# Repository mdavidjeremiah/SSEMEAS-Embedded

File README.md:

# SSMEAS: Smart Sewage Level Monitoring

ESP32 + HC-SR04 reads the sewage level and alerts locally. A FastAPI backend stores the readings, applies the alert rules and sends WhatsApp messages. A plain HTML/CSS/JS dashboard shows it live.

```
ssmeas/
├── backend/                FastAPI + SQLite
│   ├── main.py             entry point (serves the API and the dashboard)
│   ├── app/
│   │   ├── config.py       settings from environment variables / .env
│   │   ├── db.py, repo.py  database and queries
│   │   ├── security.py     passwords, login tokens, rate limiting
│   │   ├── schemas.py      request validation
│   │   ├── routers/        auth, device (ESP32), dashboard, profile, admin, webhooks, live (WebSocket)
│   │   └── services/       status (level + hysteresis), readings, notifier (WhatsApp, email), realtime, watcher
│   ├── tests/              pytest suite
│   └── simulate.py         pretends to be the ESP32
├── frontend/               no framework, no build step (ES modules)
│   ├── index.html, css/styles.css
│   └── js/                 main, auth, service, remote (real API), mock (demo), store, ui, views/
└── firmware/ssmeas_esp32/  Arduino sketch: config.h (edit this), sensor.h, alerts.h, network.h
```

## Run it

```
cd backend
pip install -r requirements.txt
uvicorn main:app --host 0.0.0.0 --port 8000
```

Open http://localhost:8000. First run creates `ssmeas.db`, an admin (`admin@example.com` / `admin123`) and a demo tank whose device key is `dev-device-key`. Change all three before deploying (see `.env.example`).

`--host 0.0.0.0` matters: without it the ESP32 cannot reach the backend, only your own computer can.

- **Try the dashboard without a backend:** serve the `frontend` folder (for example `python -m http.server` inside it) and open `/?mock=1`. It runs simulated tanks in the browser. The page uses ES modules, so it must be served over http, not opened as a file.
- **Try the backend without hardware:** `python backend/simulate.py` posts fake readings every 2 seconds.
- **Run the tests:** `pip install -r requirements-dev.txt && pytest` inside `backend/`.

## Connect the ESP32

1. Dashboard, Admin, Add a tank. Copy the **device key** (shown once).
2. Open `firmware/ssmeas_esp32/config.h` and set the Wi-Fi name and password, `SERVER_URL` (your computer's LAN IP, for example `http://192.168.1.50:8000`), `DEVICE_KEY`, and the tank depth, offset and thresholds (same as in Admin).
3. Arduino IDE: board **ESP32 Dev Module**, upload, open the Serial Monitor at 115200 baud. You should see `POST /api/v1/readings -> 201`.

Wiring: HC-SR04 TRIG to GPIO 5, ECHO to GPIO 18 **through a 1k/2k divider**, LEDs on 25/26/27, buzzer transistor on 14. Pins are constants in `config.h`.

## Configuration (environment variables or `backend/.env`)

| Variable | Purpose |
| --- | --- |
| `JWT_SECRET` | Signing key for login tokens. Required in production |
| `ADMIN_EMAIL`, `ADMIN_PASSWORD`, `DEMO_DEVICE_KEY` | First-run seed values |
| `WA_TOKEN`, `WA_PHONE_ID` | WhatsApp Cloud API. Unset means a dry run (messages print to the console) |
| `WA_ALERT_TEMPLATE` (`tank_alert`), `WA_CODE_TEMPLATE` (`verify_code`) | Approved template names. `tank_alert` has 4 body variables: tank, level %, status, time. `verify_code` has 1: the code |
| `WA_VERIFY_TOKEN`, `WA_APP_SECRET` | Webhook `/api/v1/webhooks/whatsapp` for delivery receipts |
| `SMTP_HOST`, `SMTP_PORT`, `SMTP_USER`, `SMTP_PASS`, `SMTP_FROM` | Password-reset email. Unset means the link prints to the console |
| `BASE_URL` | Public URL used in reset links |
| `REMINDER_MINUTES` (30), `RETENTION_DAYS` (90), `TZ_NAME` (Africa/Kampala) | Reminder interval, how long raw readings are kept, timezone for quiet hours |

## API summary (`/api/v1`, interactive docs at `/docs`)

| Who | Endpoints |
| --- | --- |
| ESP32 (header `X-API-Key`) | `POST /readings`, `POST /readings/batch` |
| Signed-in users | `GET /tanks`, `/tanks/{id}/readings`, `/tanks/{id}/stats`, `/tanks/{id}/export.csv`, `/alerts`, `POST /alerts/{id}/ack`, `/me*`, WebSocket `/ws` |
| Admins | `/admin/users`, `/admin/tanks`, `/admin/notifications` |
| Public | `POST /auth/register`, `/auth/login`, `/auth/forgot`, `/auth/reset`, `GET /health` |

## Before going live

- Set `JWT_SECRET`, change the admin password, and replace the demo device key.
- Use HTTPS. Set `USE_TLS 1` in the firmware and load your server's root certificate instead of `setInsecure()`.
- SQLite on free hosting may be wiped on redeploy. Use a persistent disk or move `db.py` to PostgreSQL.
- Register the two WhatsApp templates and confirm current Meta pricing and API version.
- Check the sensor against a tape measure at two or three levels and correct the depth and offset.

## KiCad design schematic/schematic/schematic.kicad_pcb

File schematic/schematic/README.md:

# SSEMAS Smart Sewage Monitoring Carrier

This directory contains the editable KiCad 10 schematic and routed two-layer PCB for the module-level system shown in the wiring reference:

- ESP32 DevKit V1
- HC-SR04 ultrasonic sensor
- SIM800L module
- external LM2596 buck converter, adjusted to 4.0 V
- transistor-driven 5 V buzzer
- green, yellow, and red status LEDs

Open `schematic.kicad_pro` in KiCad. The main editable sources are:

- `schematic.kicad_sch` — self-contained schematic with embedded project symbols
- `schematic.kicad_pcb` — placed, routed, copper-filled PCB
- `HC-SR04.pretty/TH_HC-SR04V.kicad_mod` — project-local ultrasonic sensor footprint
- `ssemas.kicad_sym` — reusable project symbol library

## Interface pin order

### J2 — LM2596 module

1. IN+ / 12 V
2. IN- / GND
3. OUT- / GND
4. OUT+ / 4.0 V

### J3 — ESP32 DevKit cable

1. VIN/5V from USB
2. GND
3. GPIO5 — HC-SR04 TRIG
4. GPIO18 — divided HC-SR04 ECHO
5. GPIO16/RX — SIM800L TXD
6. GPIO17/TX — SIM800L RXD divider
7. GPIO25 — buzzer
8. GPIO2 — green LED
9. GPIO4 — yellow LED
10. GPIO26 — red LED
11. reserved / no connection

### J4 — SIM800L module

1. VCC / 4.0 V
2. GND
3. TXD
4. RXD
5. RST / no connection

## Electrical notes

- Adjust the LM2596 output to **4.0 V before installing the SIM800L**.
- Power the ESP32 DevKit from USB. J3 pin 1 carries that 5 V rail to the HC-SR04 and buzzer.
- C1 is a 1000 uF low-ESR reservoir capacitor for SIM800L transmit-current bursts.
- The HC-SR04 ECHO divider is 2.2 kΩ / 3.3 kΩ, producing about 3.0 V from a 5 V echo signal.
- The SIM800L RX divider is 10 kΩ / 20 kΩ, producing about 2.2 V from the ESP32's 3.3 V TX signal.
- All module grounds are common.
- J3 is a labeled cable interface because ESP32 DevKit clones vary; verify the actual board pin labels before wiring the cable.

## Validation

The generated design passes KiCad 10 checks:

- ERC: 0 errors, 0 warnings
- DRC: 0 violations, 0 unconnected pads, 0 footprint errors

Reports are in `reports/`. Gerber and drill files are in `fabrication/`.

## Regeneration

The deterministic generators are retained for maintainability:

```bash
python3 generate_schematic.py
python3 generate_pcb.py
```

They require KiCad 10 and its Python `pcbnew` module.

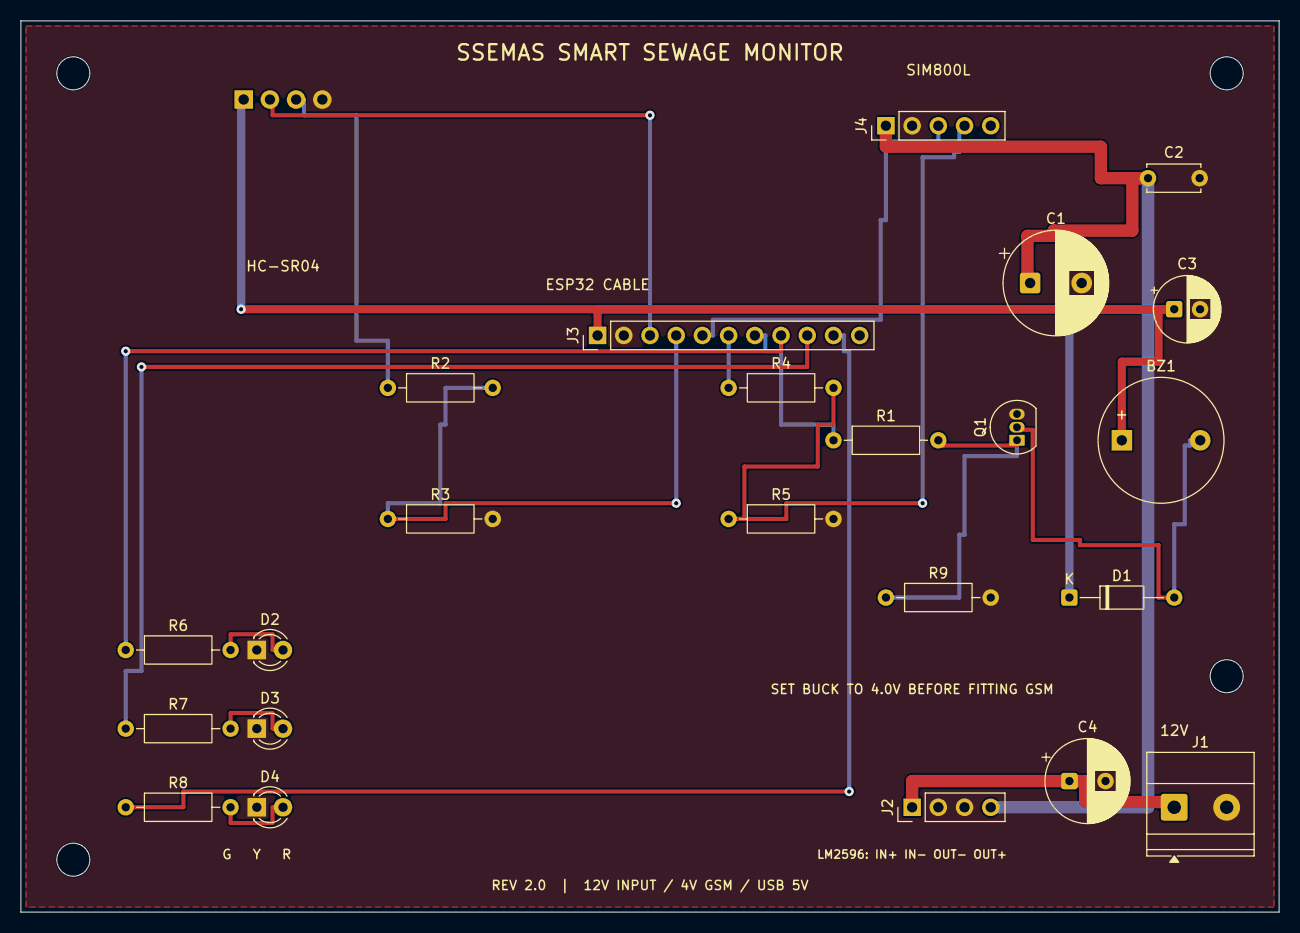
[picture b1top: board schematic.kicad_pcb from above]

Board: 2 copper layers, 121.9 x 86.4 mm, 28 parts (0 on the bottom side), 19 nets.

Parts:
BZ1: 5V ACTIVE; Buzzer_12x9.5RM7.6
C1: 1000uF LOW-ESR; CP_Radial_D10.0mm_P5.00mm
C2: 100nF; C_Disc_D5.0mm_W2.5mm_P5.00mm
C3: 100uF; CP_Radial_D6.3mm_P2.50mm
C4: 100uF 25V; CP_Radial_D8.0mm_P3.50mm
D1: 1N4148; D_DO-35_SOD27_P10.16mm_Horizontal
D2: GREEN; LED_D3.0mm
D3: YELLOW; LED_D3.0mm
D4: RED; LED_D3.0mm
H1, H2, H3, H4: MountingHole_3.2mm_M3
J1: 12V INPUT; TerminalBlock_Phoenix_MKDS-1,5-2-5.08_1x02_P5.08mm_Horizont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
J2: LM2596; PinHeader_1x04_P2.54mm_Vertical
J3: ESP32 DEVKIT; PinHeader_1x11_P2.54mm_Vertical
J4: SIM800L; PinHeader_1x05_P2.54mm_Vertical
Q1: 2N2222; TO-92_Inline
R1: 1k; R_Axial_DIN0207_L6.3mm_D2.5mm_P10.16mm_Horizontal
R2: 2.2k; R_Axial_DIN0207_L6.3mm_D2.5mm_P10.16mm_Horizontal
R3: 3.3k; R_Axial_DIN0207_L6.3mm_D2.5mm_P10.16mm_Horizontal
R4: 10k; R_Axial_DIN0207_L6.3mm_D2.5mm_P10.16mm_Horizontal
R5: 20k; R_Axial_DIN0207_L6.3mm_D2.5mm_P10.16mm_Horizontal
R6, R7, R8: 330; R_Axial_DIN0207_L6.3mm_D2.5mm_P10.16mm_Horizontal
R9: 100k; R_Axial_DIN0207_L6.3mm_D2.5mm_P10.16mm_Horizontal
U1: HC-SR04; TH_HC-SR04V

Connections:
+4V_GSM: C1.1, C2.1, J2.4, J4.1
+5V_USB: BZ1.1, C3.1, D1.1, J3.1, U1.1
+12V_IN: C4.1, J1.1, J2.1
BUZZ_BASE: Q1.1, R1.2, R9.1
BUZZ_CTRL: J3.7, R1.1
BUZZ_SW: BZ1.2, D1.2, Q1.2
ESP_TXD_3V3: J3.6, R4.1
GND: C1.2, C2.2, C3.2, C4.2, D2.1, D3.1, D4.1, J1.2, J2.2, J2.3, J3.2, J4.2, Q1.3, R3.2, R5.2, R9.2, U1.4
GPIO2_GREEN: J3.8, R6.1
GPIO4_YELLOW: J3.9, R7.1
GPIO26_RED: J3.10, R8.1
HC_ECHO_3V3: J3.4, R2.2, R3.1
HC_ECHO_RAW: R2.1, U1.3
HC_TRIG: J3.3, U1.2
LED_GREEN_A: D2.2, R6.2
LED_RED_A: D4.2, R8.2
LED_YELLOW_A: D3.2, R7.2
SIM_RXD: J4.4, R4.2, R5.1
SIM_TXD: J3.5, J4.3

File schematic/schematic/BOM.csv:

"References","Value","Footprint","Quantity"
"BZ1","5V_ACTIVE_BUZZER","Buzzer_Beeper:Buzzer_12x9.5RM7.6","1"
"C1","1000uF LOW-ESR","Capacitor_THT:CP_Radial_D10.0mm_P5.00mm","1"
"C2","100nF","Capacitor_THT:C_Disc_D5.0mm_W2.5mm_P5.00mm","1"
"C3","100uF","Capacitor_THT:CP_Radial_D6.3mm_P2.50mm","1"
"C4","100uF 25V","Capacitor_THT:CP_Radial_D8.0mm_P3.50mm","1"
"D1","1N4148","Diode_THT:D_DO-35_SOD27_P10.16mm_Horizontal","1"
"D2","GREEN","LED_THT:LED_D3.0mm","1"
"D3","YELLOW","LED_THT:LED_D3.0mm","1"
"D4","RED","LED_THT:LED_D3.0mm","1"
"J1","12V_INPUT","TerminalBlock_Phoenix:TerminalBlock_Phoenix_MKDS-1,5-2-5.08_1x02_P5.08mm_Horizontal","1"
"J2","LM2596_MODULE","Connector_PinHeader_2.54mm:PinHeader_1x04_P2.54mm_Vertical","1"
"J3","ESP32_DEVKIT_INTERFACE","Connector_PinHeader_2.54mm:PinHeader_1x11_P2.54mm_Vertical","1"
"J4","SIM800L_MODULE","Connector_PinHeader_2.54mm:PinHeader_1x05_P2.54mm_Vertical","1"
"Q1","2N2222","Package_TO_SOT_THT:TO-92_Inline","1"
"R1","1k","Resistor_THT:R_Axial_DIN0207_L6.3mm_D2.5mm_P10.16mm_Horizontal","1"
"R2","2.2k","Resistor_THT:R_Axial_DIN0207_L6.3mm_D2.5mm_P10.16mm_Horizontal","1"
"R3","3.3k","Resistor_THT:R_Axial_DIN0207_L6.3mm_D2.5mm_P10.16mm_Horizontal","1"
"R4","10k","Resistor_THT:R_Axial_DIN0207_L6.3mm_D2.5mm_P10.16mm_Horizontal","1"
"R5","20k","Resistor_THT:R_Axial_DIN0207_L6.3mm_D2.5mm_P10.16mm_Horizontal","1"
"R6-R8","330","Resistor_THT:R_Axial_DIN0207_L6.3mm_D2.5mm_P10.16mm_Horizontal","3"
"R9","100k","Resistor_THT:R_Axial_DIN0207_L6.3mm_D2.5mm_P10.16mm_Horizontal","1"
"U1","HC-SR04","HC-SR04:TH_HC-SR04V","1"

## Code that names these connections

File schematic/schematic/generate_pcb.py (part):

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NETS = [
    "GND", "+12V_IN", "+4V_GSM", "+5V_USB", "HC_TRIG",
    "HC_ECHO_RAW", "HC_ECHO_3V3", "SIM_TXD", "ESP_TXD_3V3",
    "SIM_RXD", "BUZZ_CTRL", "BUZZ_BASE", "BUZZ_SW", "GPIO2_GREEN",
    "LED_GREEN_A", "GPIO4_YELLOW", "LED_YELLOW_A", "GPIO26_RED",
    "LED_RED_A",
]

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    # ref, library, footprint, value, x, y, rotation, pad-to-net mapping
    ("U1", str(ROOT / "HC-SR04.pretty"), "TH_HC-SR04V", "HC-SR04", 45.72, 22.86, 0, {"1": "+5V_USB", "2": "HC_TRIG", "3": "HC_ECHO_RAW", "4": "GND"}),
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    ("J4", str(FP_ROOT / "Connector_PinHeader_2.54mm.pretty"), "PinHeader_1x05_P2.54mm_Vertical", "SIM800L", 104.14, 25.40, 90, {"1": "+4V_GSM", "2": "GND", "3": "SIM_TXD", "4": "SIM_RXD"}),
    ("J2", str(FP_ROOT / "Connector_PinHeader_2.54mm.pretty"), "PinHeader_1x04_P2.54mm_Vertical", "LM2596", 106.68, 91.44, 90, {"1": "+12V_IN", "2": "GND", "3": "GND", "4": "+4V_GSM"}),
    ("J1", str(FP_ROOT / "TerminalBlock_Phoenix.pretty"), "TerminalBlock_Phoenix_MKDS-1,5-2-5.08_1x02_P5.08mm_Horizontal", "12V INPUT", 132.08, 91.44, 0, {"1": "+12V_IN", "2": "GND"}),
    ("R2", str(FP_ROOT / "Resistor_THT.pretty"), "R_Axial_DIN0207_L6.3mm_D2.5mm_P10.16mm_Horizontal", "2.2k", 55.88, 50.80, 0, {"1": "HC_ECHO_RAW", "2": "HC_ECHO_3V3"}),
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    ("Q1", str(FP_ROOT / "Package_TO_SOT_THT.pretty"), "TO-92_Inline", "2N2222", 116.84, 55.88, 90, {"1": "BUZZ_BASE", "2": "BUZZ_SW", "3": "GND"}),
    ("BZ1", str(FP_ROOT / "Buzzer_Beeper.pretty"), "Buzzer_12x9.5RM7.6", "5V ACTIVE", 127.00, 55.88, 0, {"1": "+5V_USB", "2": "BUZZ_SW"}),
    ("D1", str(FP_ROOT / "Diode_THT.pretty"), "D_DO-35_SOD27_P10.16mm_Horizontal", "1N4148", 121.92, 71.12, 0, {"1": "+5V_USB", "2": "BUZZ_SW"}),
    ("R6", str(FP_ROOT / "Resistor_THT.pretty"), "R_Axial_DIN0207_L6.3mm_D2.5mm_P10.16mm_Horizontal", "330", 30.48, 76.20, 0, {"1": "GPIO2_GREEN", "2": "LED_GREEN_A"}),
    ("D2", str(FP_ROOT / "LED_THT.pretty"), "LED_D3.0mm", "GREEN", 43.18, 76.20, 0, {"1": "GND", "2": "LED_GREEN_A"}),
    ("R7", str(FP_ROOT / "Resistor_THT.pretty"), "R_Axial_DIN0207_L6.3mm_D2.5mm_P10.16mm_Horizontal", "330", 30.48, 83.82, 0, {"1": "GPIO4_YELLOW", "2": "LED_YELLOW_A"}),
    ("D3", str(FP_ROOT / "LED_THT.pretty"), "LED_D3.0mm", "YELLOW", 43.18, 83.82, 0, {"1": "GND", "2": "LED_YELLOW_A"}),
    ("R8", str(FP_ROOT / "Resistor_THT.pretty"), "R_Axial_DIN0207_L6.3mm_D2.5mm_P10.16mm_Horizontal", "330", 30.48, 91.44, 0, {"1": "GPIO26_RED", "2": "LED_RED_A"}),
    ("D4", str(FP_ROOT / "LED_THT.pretty"), "LED_D3.0mm", "RED", 43.18, 91.44, 0, {"1": "GND", "2": "LED_RED_A"}),
    ("C1", str(FP_ROOT / "Capacitor_THT.pretty"), "CP_Radial_D10.0mm_P5.00mm", "1000uF LOW-ESR", 118.11, 40.64, 0, {"1": "+4V_GSM", "2": "GND"}),
    ("C2", str(FP_ROOT / "Capacitor_THT.pretty"), "C_Disc_D5.0mm_W2.5mm_P5.00mm", "100nF", 129.54, 30.48, 0, {"1": "+4V_GSM", "2": "GND"}),
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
